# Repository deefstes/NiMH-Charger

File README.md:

# NiMH-Charger
KiCAD project for a 4 cell NiMH Charger

This project is largely based on information gathered from these two sources:
http://www.allaboutcircuits.com/projects/create-an-arduino-controlled-battery-charger/
http://electronics.stackexchange.com/questions/8744/voltage-input-for-charging-nimh-batteries

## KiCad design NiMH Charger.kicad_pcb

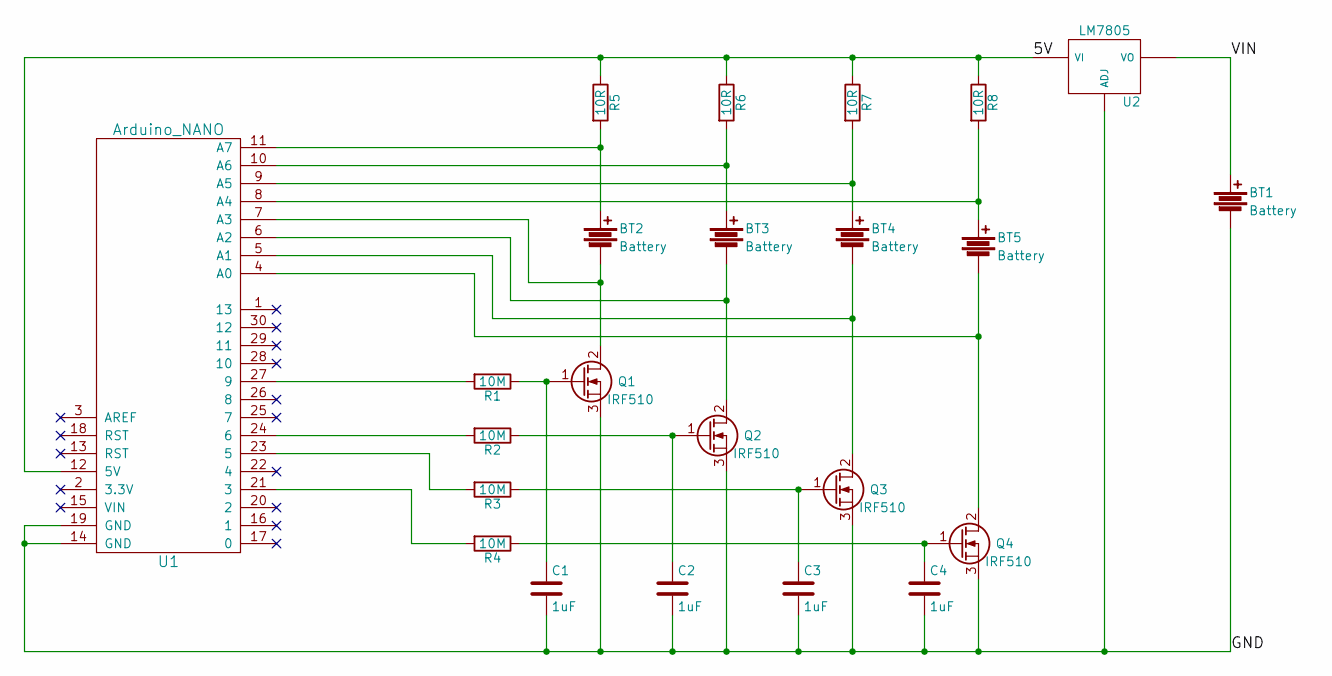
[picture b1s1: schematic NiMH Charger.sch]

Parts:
BT1: Battery; TerminalBlock_Pheonix_MKDS1.5-2pol
BT2, BT3, BT4, BT5: Battery; PINHEAD1-2
C1, C2, C3, C4: 1uF; C_Disc_D6_P5
Q1, Q2, Q3, Q4: IRF510; TO-220_Neutral123_Vertical_LargePads
R1, R2, R3, R4: 10M; R1
R5, R6, R7, R8: 10R; Resistor_Ceramic_Horizontal_L23mm-W9mm-H9mm-p30mm
U1: Arduino_NANO
U2: LM7805; TO-220_Neutral123_Vertical

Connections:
/5V: R5.1, R6.1, R7.1, R8.1, U1.12 (5V), U2.1 (VI)
/GND: BT1.2, C1.2, C2.2, C3.2, C4.2, Q1.3 (S), Q2.3 (S), Q3.3 (S), Q4.3 (S), U1.14 (GND), U1.19 (GND), U2.2 (ADJ)
/VIN: BT1.1, U2.3 (VO)
unnamed: BT2.1, R5.2, U1.11 (A7)
unnamed: BT2.2, Q1.2 (D), U1.7 (A3)
unnamed: BT3.1, R6.2, U1.10 (A6)
unnamed: BT3.2, Q2.2 (D), U1.6 (A2)
unnamed: BT4.1, R7.2, U1.9 (A5)
unnamed: BT4.2, Q3.2 (D), U1.5 (A1)
unnamed: BT5.1, R8.2, U1.8 (A4)
unnamed: BT5.2, Q4.2 (D), U1.4 (A0)
unnamed: C1.1, Q1.1 (G), R1.1
unnamed: C2.1, Q2.1 (G), R2.1
unnamed: C3.1, Q3.1 (G), R3.1
unnamed: C4.1, Q4.1 (G), R4.1
unnamed: R1.2, U1.27 (9)
unnamed: R2.2, U1.24 (6)
unnamed: R3.2, U1.23 (5)
unnamed: R4.2, U1.21 (3)

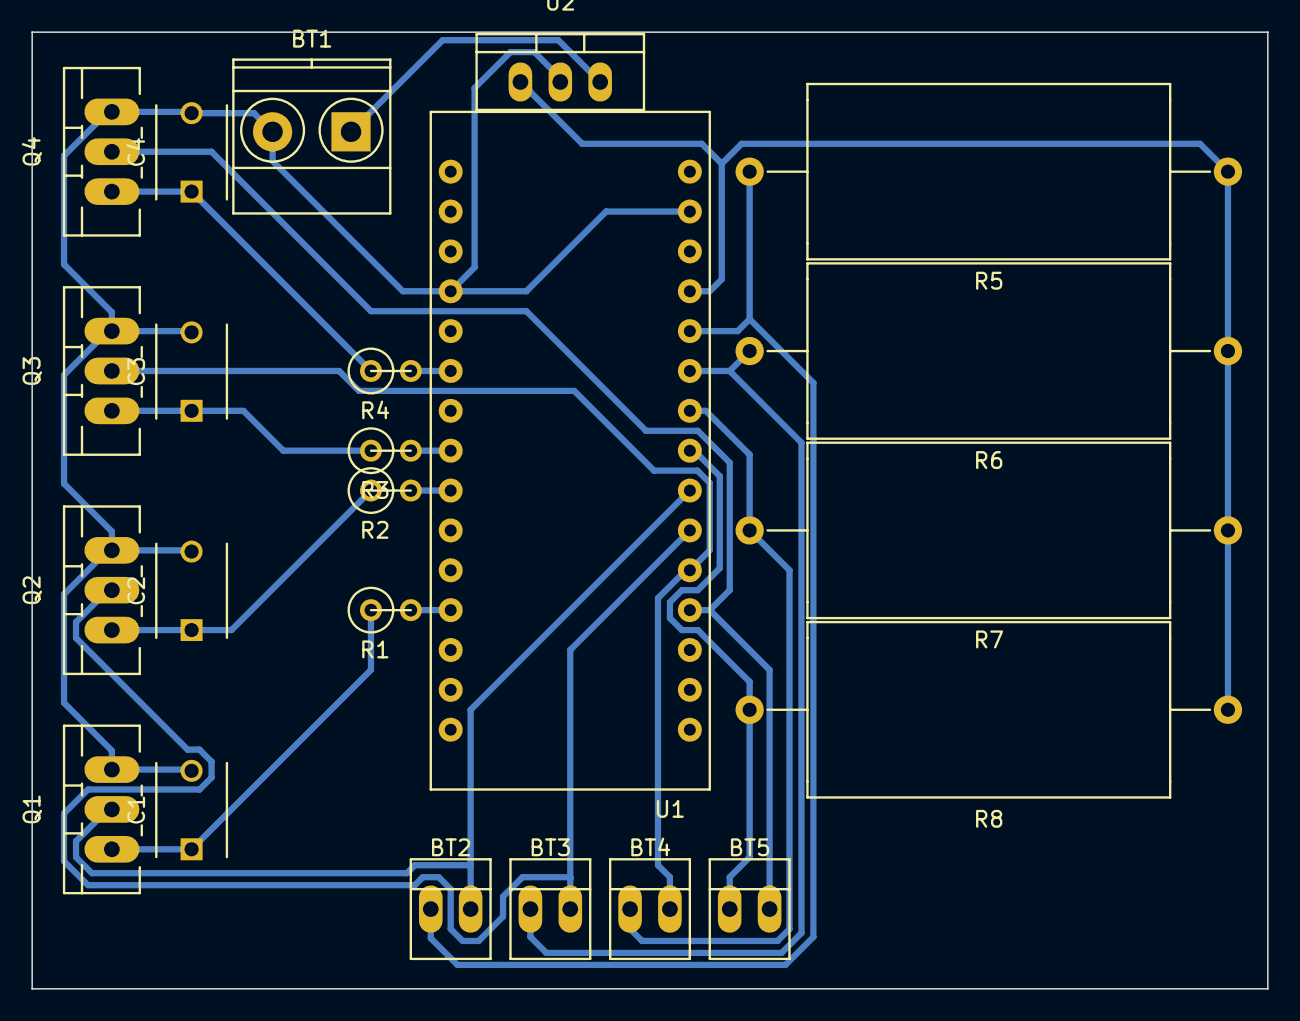
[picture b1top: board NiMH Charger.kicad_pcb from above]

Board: 2 copper layers, 78.7 x 61.0 mm, 23 parts (0 on the bottom side), 19 nets.

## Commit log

2016-12-22 Removing .dsn and .ses files
2016-12-22 Removed 7805 Voltage Regulator
    Unsure whether 7805 will be able to provide the necessary current should all four cells be charging simultaneously at highest current. The circuit now relies on a regulated 5V supply voltage.
